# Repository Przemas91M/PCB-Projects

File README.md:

# PCB-Projects
Płytki PCB dla moich projektów.

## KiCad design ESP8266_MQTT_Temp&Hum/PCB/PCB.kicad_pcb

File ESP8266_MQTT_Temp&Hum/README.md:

# ESP8266 Smart sensor
Płytka PCB dla Smart Sensora z repozytorium:
https://github.com/Przemas91M/ESP8266_SmartSensor

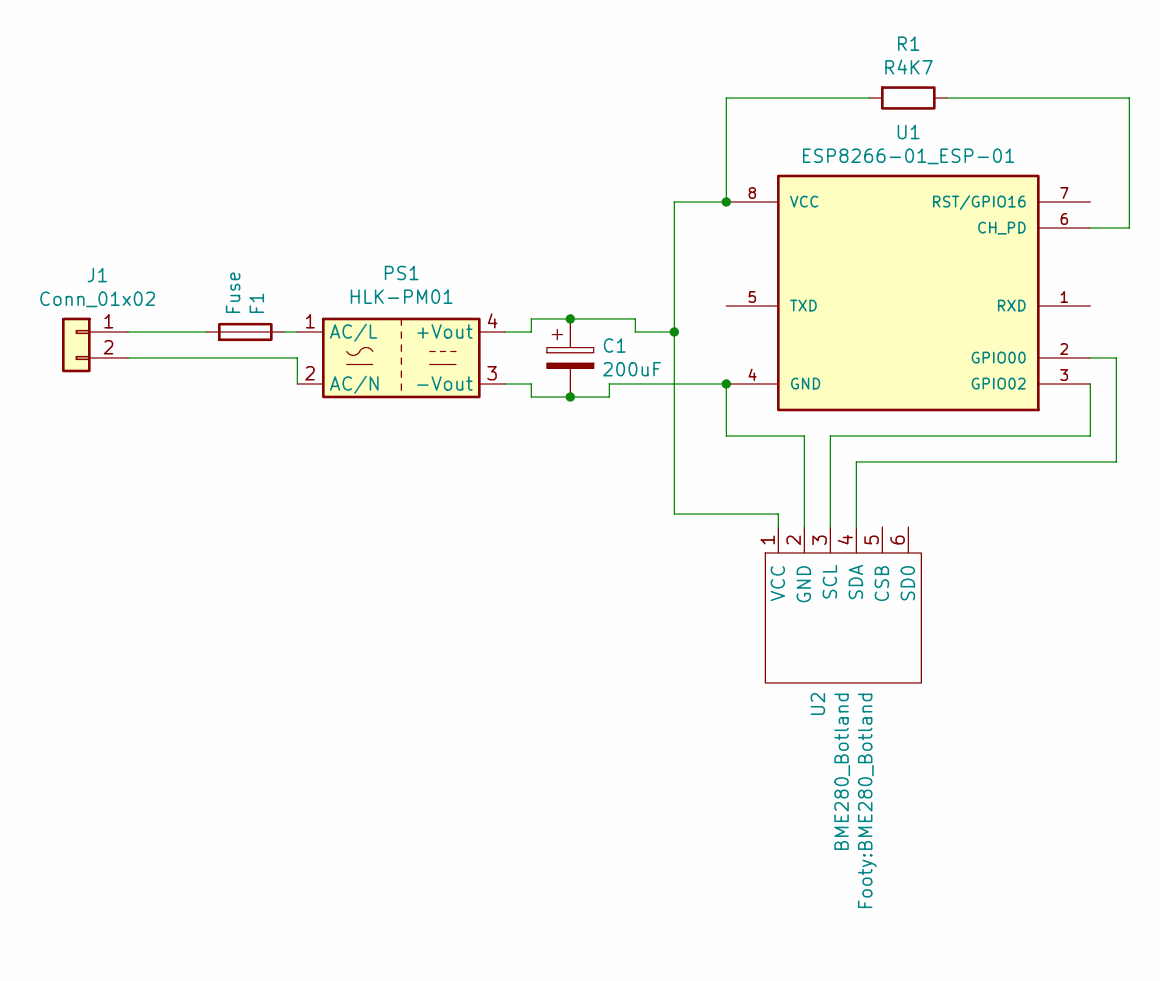
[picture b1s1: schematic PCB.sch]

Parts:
C1: 200uF; CP_Radial_D5.0mm_P2.50mm
F1: Fuse; FuseHolder PTF-78
J1: Conn_01x02; TerminalBlock_bornier-2_P5.08mm
PS1: HLK-PM01; Converter_ACDC_HiLink_HLK-PMxx
R1: R4K7; R_Axial_DIN0204_L3.6mm_D1.6mm_P5.08mm_Horizontal
U1: ESP8266-01_ESP-01; ESP-01
U2: BME280_Botland

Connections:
unnamed: C1.1, PS1.4 (+Vout), R1.2, U1.8 (VCC), U2.1 (VCC)
unnamed: C1.2, PS1.3 (-Vout), U1.4 (GND), U2.2 (GND)
unnamed: F1.1, PS1.1 (AC/L)
unnamed: F1.2, J1.1
unnamed: J1.2, PS1.2 (AC/N)
unnamed: R1.1, U1.6 (CH_PD)
unnamed: U1.2 (GPIO00), U2.4 (SDA)
unnamed: U1.3 (GPIO02), U2.3 (SCL)

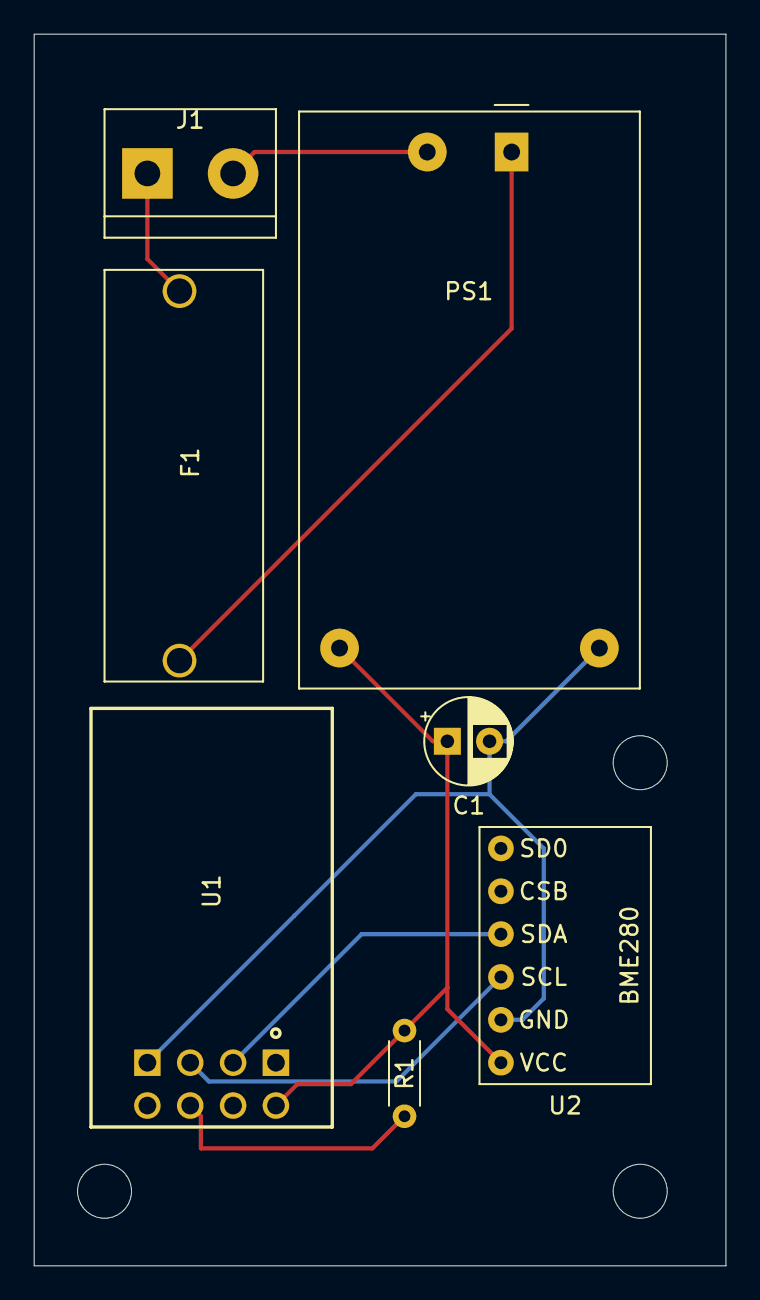
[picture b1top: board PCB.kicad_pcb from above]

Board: 2 copper layers, 41.0 x 73.0 mm, 10 parts (0 on the bottom side), 8 nets.

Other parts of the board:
M1, M2, M3: MountingHole_3.2mm_M3

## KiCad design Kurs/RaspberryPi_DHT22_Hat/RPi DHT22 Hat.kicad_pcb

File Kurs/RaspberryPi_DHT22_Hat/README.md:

# Raspberry Pi DHT22 Hat
Nakładka na mikrokomputer Raspberry Pi, zawierająca czujnik temperatury i wilgotności DHT22 oraz przycisk tact switch.
Wykonano na zajęciach online kursu projektowania płytek PCB.

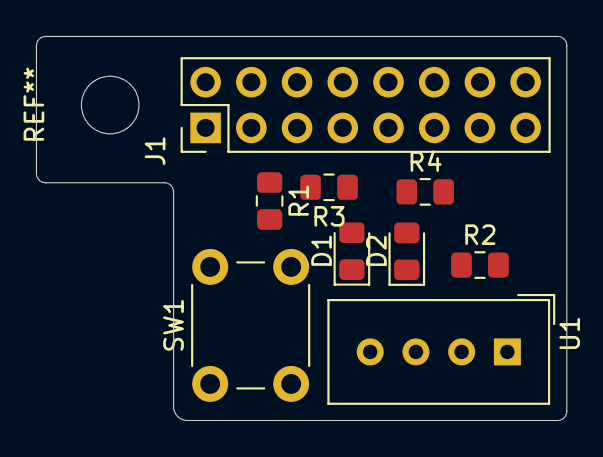
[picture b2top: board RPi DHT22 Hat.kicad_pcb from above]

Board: 2 copper layers, 29.5 x 21.3 mm, 9 parts (0 on the bottom side), 7 nets, no tracks yet.

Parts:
D1, D2: LED; LED_0805_2012Metric_Pad1.15x1.40mm_HandSolder
J1: Raspberry_Pi_2_3; PinHeader_2x08_P2.54mm_Vertical
R1, R2: 10K; R_0805_2012Metric_Pad1.15x1.40mm_HandSolder
R3, R4: 330R; R_0805_2012Metric_Pad1.15x1.40mm_HandSolder
SW1: SW_DPST; SW_PUSH_6mm
U1: DHT22; Aosong_DHT11_5.5x12.0_P2.54mm

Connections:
+3V3: J1.1, R2.2, R4.2, SW1.1, U1.1
/button_input: J1.8, R1.2, SW1.2
GND: D1.1, D2.1, J1.6, J1.9, R1.1, U1.4
unnamed: D1.2, R3.1
unnamed: D2.2, R4.1
unnamed: J1.7, R3.2
unnamed: J1.11, R2.1, U1.2

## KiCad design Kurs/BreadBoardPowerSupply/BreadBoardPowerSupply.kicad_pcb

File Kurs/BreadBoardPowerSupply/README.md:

# Breadboard Power Supply
Projekt zasilacza płytek prototypowych.
Wykonano na zajęciach online kursu projektowania płytek PCB.

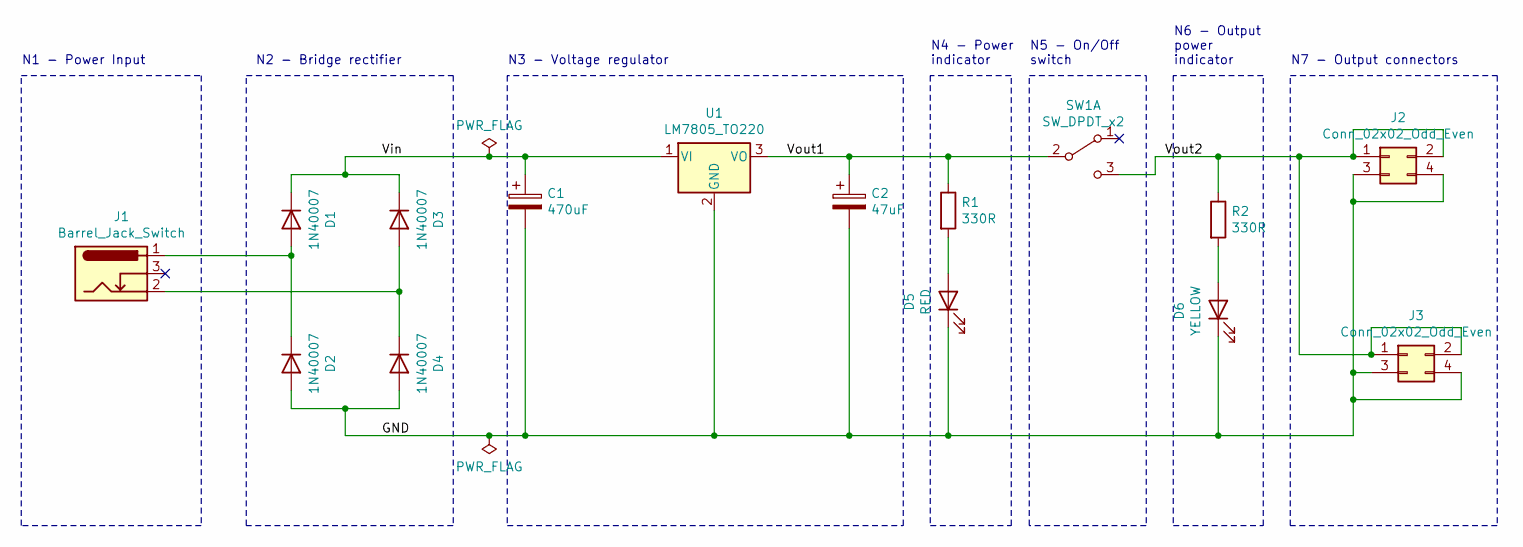
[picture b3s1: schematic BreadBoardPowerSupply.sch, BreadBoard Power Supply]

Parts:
C1: 470uF; CP_Radial_D10.0mm_P5.00mm
C2: 47uF; CP_Radial_D6.3mm_P2.50mm
D1, D2, D3, D4: 1N40007; D_DO-41_SOD81_P10.16mm_Horizontal
D5: RED; LED_D5.0mm
D6: YELLOW; LED_D5.0mm
J1: Barrel_Jack_Switch; BarrelJack_Horizontal
J2, J3: Conn_02x02_Odd_Even; PinHeader_2x02_P2.54mm_Vertical
R1, R2: 330R; R_Axial_DIN0207_L6.3mm_D2.5mm_P7.62mm_Horizontal
SW1: SW_DPDT_x2; Switch_Slide_11.6x4mm_EG1218
U1: LM7805_TO220; TO-220-3_Vertical

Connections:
/GND: C1.2, C2.2, D2.2 (A), D4.2 (A), D5.1 (K), D6.1 (K), J2.3, J2.4, J3.3, J3.4, U1.2 (GND)
/Vin: C1.1, D1.1 (K), D3.1 (K), U1.1 (VI)
/Vout1: C2.1, R1.1, SW1.2 (B), U1.3 (VO)
/Vout2: J2.1, J2.2, J3.1, J3.2, R2.1, SW1.3 (C)
unnamed: D1.2 (A), D2.1 (K), J1.1
unnamed: D3.2 (A), D4.1 (K), J1.2
unnamed: D5.2 (A), R1.2
unnamed: D6.2 (A), R2.2

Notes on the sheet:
N1 - Power Input
N2 - Bridge rectifier
N3 - Voltage regulator
N4 - Power indicator
N5 - On/Off switch
N6 - Output power indicator
N7 - Output connectors

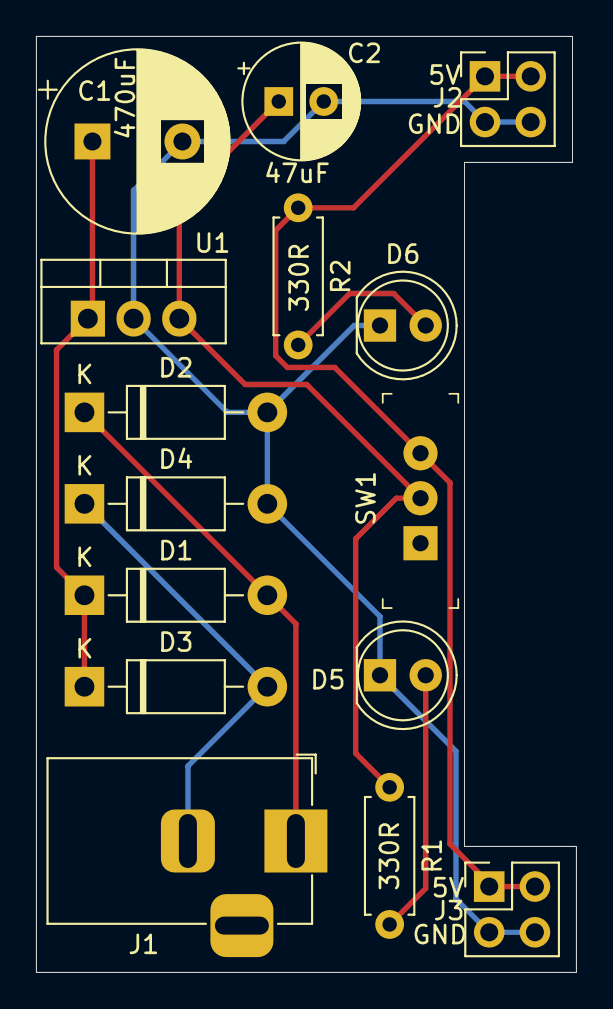
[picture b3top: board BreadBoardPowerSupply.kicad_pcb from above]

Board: 2 copper layers, 30.0 x 52.0 mm, 16 parts (1 on the bottom side), 8 nets.

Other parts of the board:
LOGO1: KiCad-Logo2_6mm_SilkScreen
